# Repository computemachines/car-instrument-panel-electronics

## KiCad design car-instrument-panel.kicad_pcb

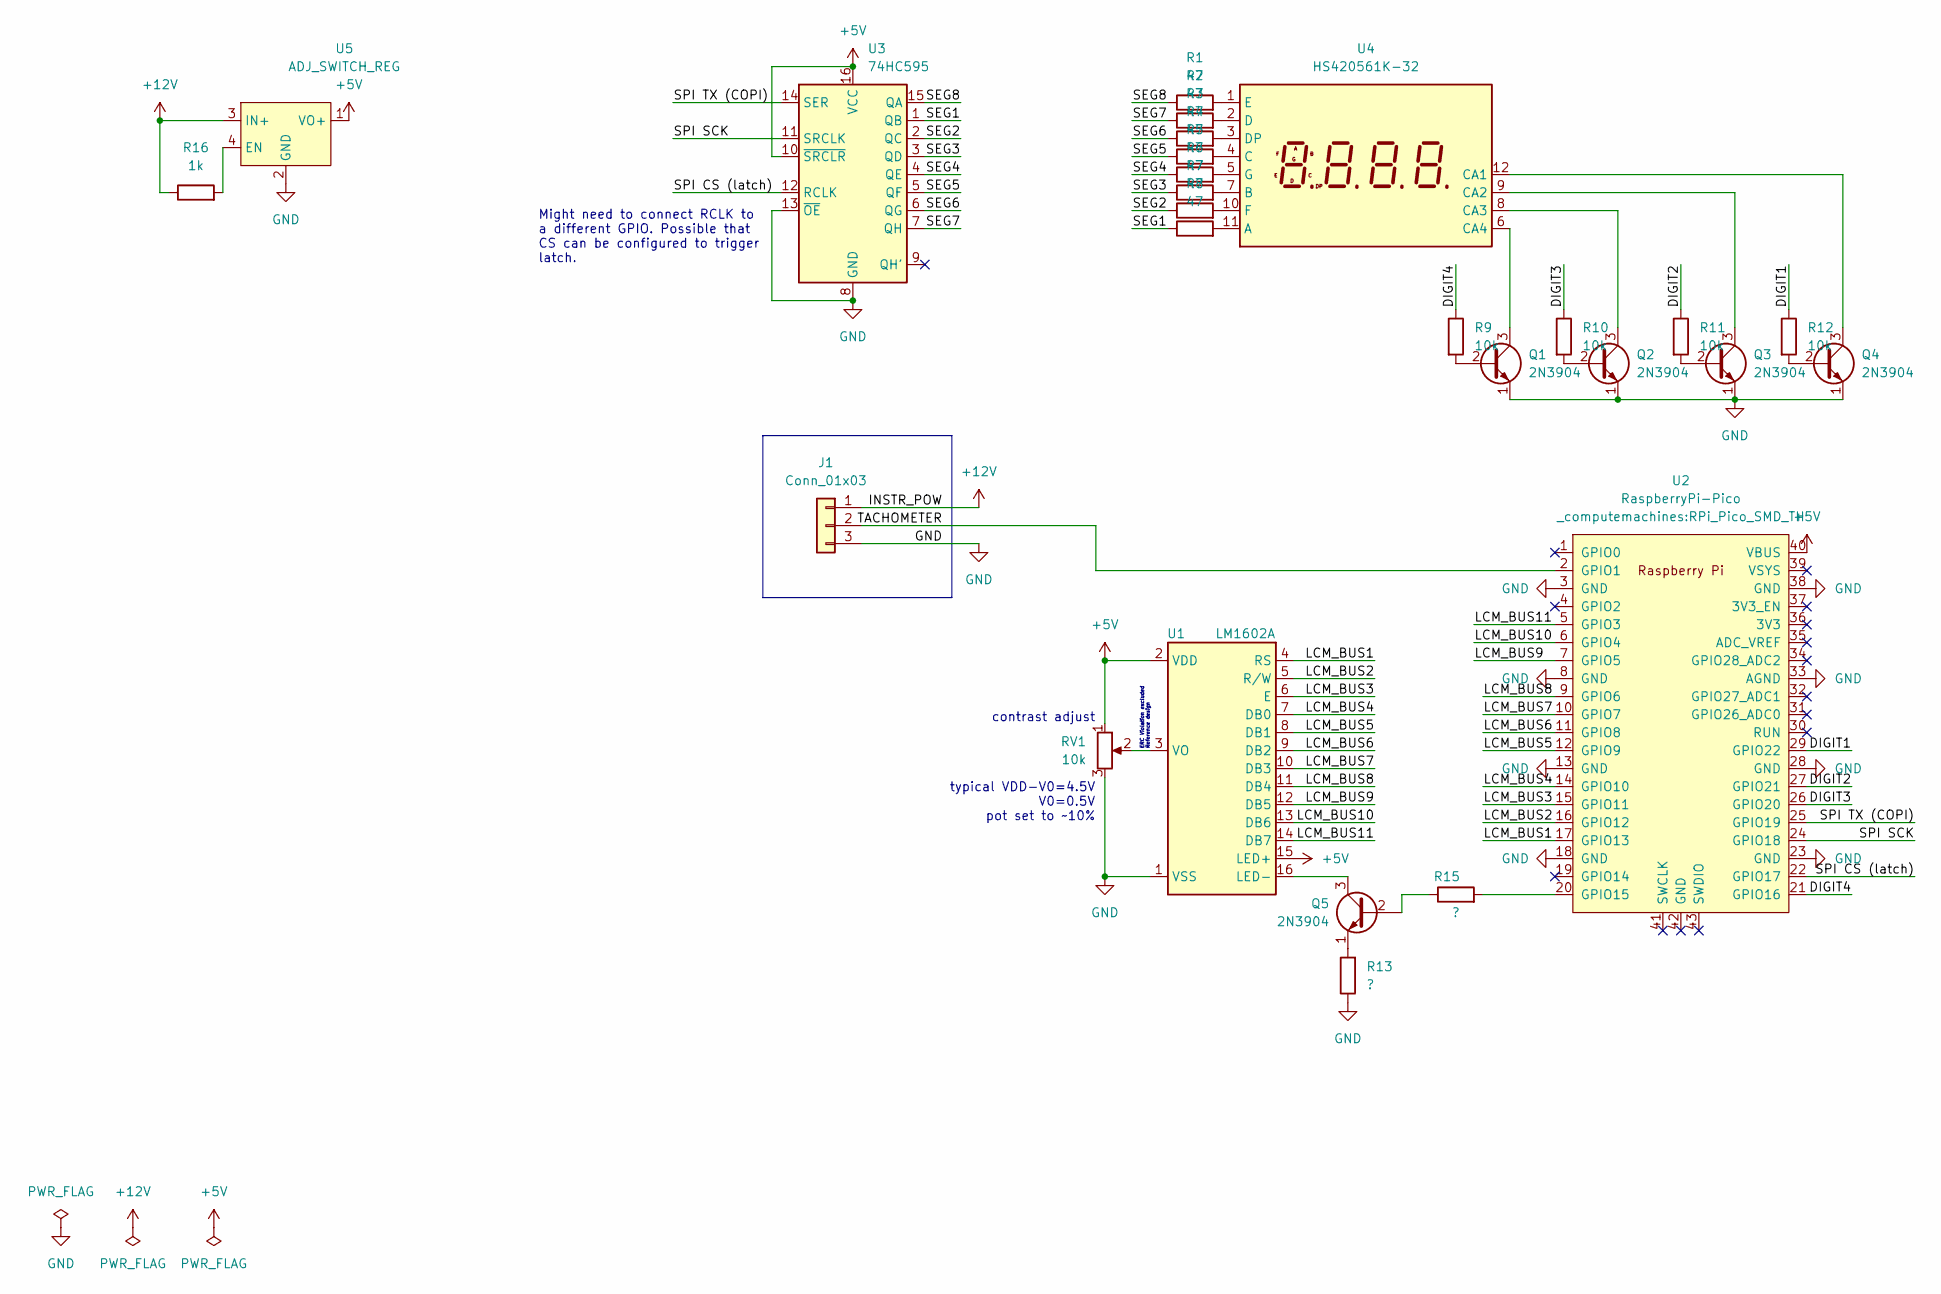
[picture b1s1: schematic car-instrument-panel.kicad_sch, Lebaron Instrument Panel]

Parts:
J1: Conn_01x03; PinHeader_1x03_P2.54mm_Vertical
Q1, Q2, Q3, Q4, Q5: 2N3904; TO-92_Inline
R1, R2, R3, R4, R5, R6, R7, R8: 47; R_Axial_DIN0207_L6.3mm_D2.5mm_P10.16mm_Horizontal
R9, R10, R11, R12: 10k; R_Axial_DIN0207_L6.3mm_D2.5mm_P10.16mm_Horizontal
R13, R15: ?; R_Axial_DIN0207_L6.3mm_D2.5mm_P10.16mm_Horizontal
R16: 1k; R_Axial_DIN0207_L6.3mm_D2.5mm_P10.16mm_Horizontal
RV1: 10k; Potentiometer_ACP_CA9-V10_Vertical
U1: LM1602A; LCM1602A
U2: RaspberryPi-Pico; RPi_Pico_SMD_TH
U3: 74HC595; DIP-16_W7.62mm
U4: HS420561K-32
U5: ADJ_SWITCH_REG; Adjust_Switch_Regulator_Module_B08R6337QY

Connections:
+5V: RV1.1, U1.2 (VDD), U1.15 (LED+), U2.40 (VBUS), U3.10 (~SRCLR), U3.16 (VCC), U5.1 (VO+)
+12V: J1.1, R16.1, U5.3 (IN+)
/DIGIT1: R12.1, U2.29 (GPIO22)
/DIGIT2: R11.1, U2.27 (GPIO21)
/DIGIT3: R10.1, U2.26 (GPIO20)
/DIGIT4: R9.1, U2.21 (GPIO16)
/LCM_BUS1: U1.4 (RS), U2.17 (GPIO13)
/LCM_BUS2: U1.5 (R/W), U2.16 (GPIO12)
/LCM_BUS3: U1.6 (E), U2.15 (GPIO11)
/LCM_BUS4: U1.7 (DB0), U2.14 (GPIO10)
/LCM_BUS5: U1.8 (DB1), U2.12 (GPIO9)
/LCM_BUS6: U1.9 (DB2), U2.11 (GPIO8)
/LCM_BUS7: U1.10 (DB3), U2.10 (GPIO7)
/LCM_BUS8: U1.11 (DB4), U2.9 (GPIO6)
/LCM_BUS9: U1.12 (DB5), U2.7 (GPIO5)
/LCM_BUS10: U1.13 (DB6), U2.6 (GPIO4)
/LCM_BUS11: U1.14 (DB7), U2.5 (GPIO3)
/SEG1: R8.1, U3.1 (QB)
/SEG2: R7.1, U3.2 (QC)
/SEG3: R6.1, U3.3 (QD)
/SEG4: R5.1, U3.4 (QE)
/SEG5: R4.1, U3.5 (QF)
/SEG6: R3.1, U3.6 (QG)
/SEG7: R2.1, U3.7 (QH)
/SEG8: R1.1, U3.15 (QA)
/SPI CS (latch): U2.22 (GPIO17), U3.12 (RCLK)
/SPI SCK: U2.24 (GPIO18), U3.11 (SRCLK)
/SPI TX (COPI): U2.25 (GPIO19), U3.14 (SER)
/TACHOMETER: J1.2, U2.2 (GPIO1)
GND: J1.3, Q1.1 (E), Q2.1 (E), Q3.1 (E), Q4.1 (E), R13.1, RV1.3, U1.1 (VSS), U2.3 (GND), U2.8 (GND), U2.13 (GND), U2.18 (GND), U2.23 (GND), U2.28 (GND), U2.33 (AGND), U2.38 (GND), U3.8 (GND), U3.13 (~OE), U5.2 (GND)
unnamed: Q1.2 (B), R9.2
unnamed: Q1.3 (C), U4.6 (CA4)
unnamed: Q2.2 (B), R10.2
unnamed: Q2.3 (C), U4.8 (CA3)
unnamed: Q3.2 (B), R11.2
unnamed: Q3.3 (C), U4.9 (CA2)
unnamed: Q4.2 (B), R12.2
unnamed: Q4.3 (C), U4.12 (CA1)
unnamed: Q5.1 (E), R13.2
unnamed: Q5.2 (B), R15.1
unnamed: Q5.3 (C), U1.16 (LED-)
unnamed: R1.2, U4.1 (E)
unnamed: R2.2, U4.2 (D)
unnamed: R3.2, U4.3 (DP)
unnamed: R4.2, U4.4 (C)
unnamed: R5.2, U4.5 (G)
unnamed: R6.2, U4.7 (B)
unnamed: R7.2, U4.10 (F)
unnamed: R8.2, U4.11 (A)
unnamed: RV1.2, U1.3 (VO)
unnamed: R15.2, U2.20 (GPIO15)
unnamed: R16.2, U5.4 (EN)

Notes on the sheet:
typical VDD-V0=4.5V V0=0.5V pot set to ~10%
ERC Violation excluded Reference design
contrast adjust
Might need to connect RCLK to a different GPIO. Possible that CS can be configured to trigger latch.

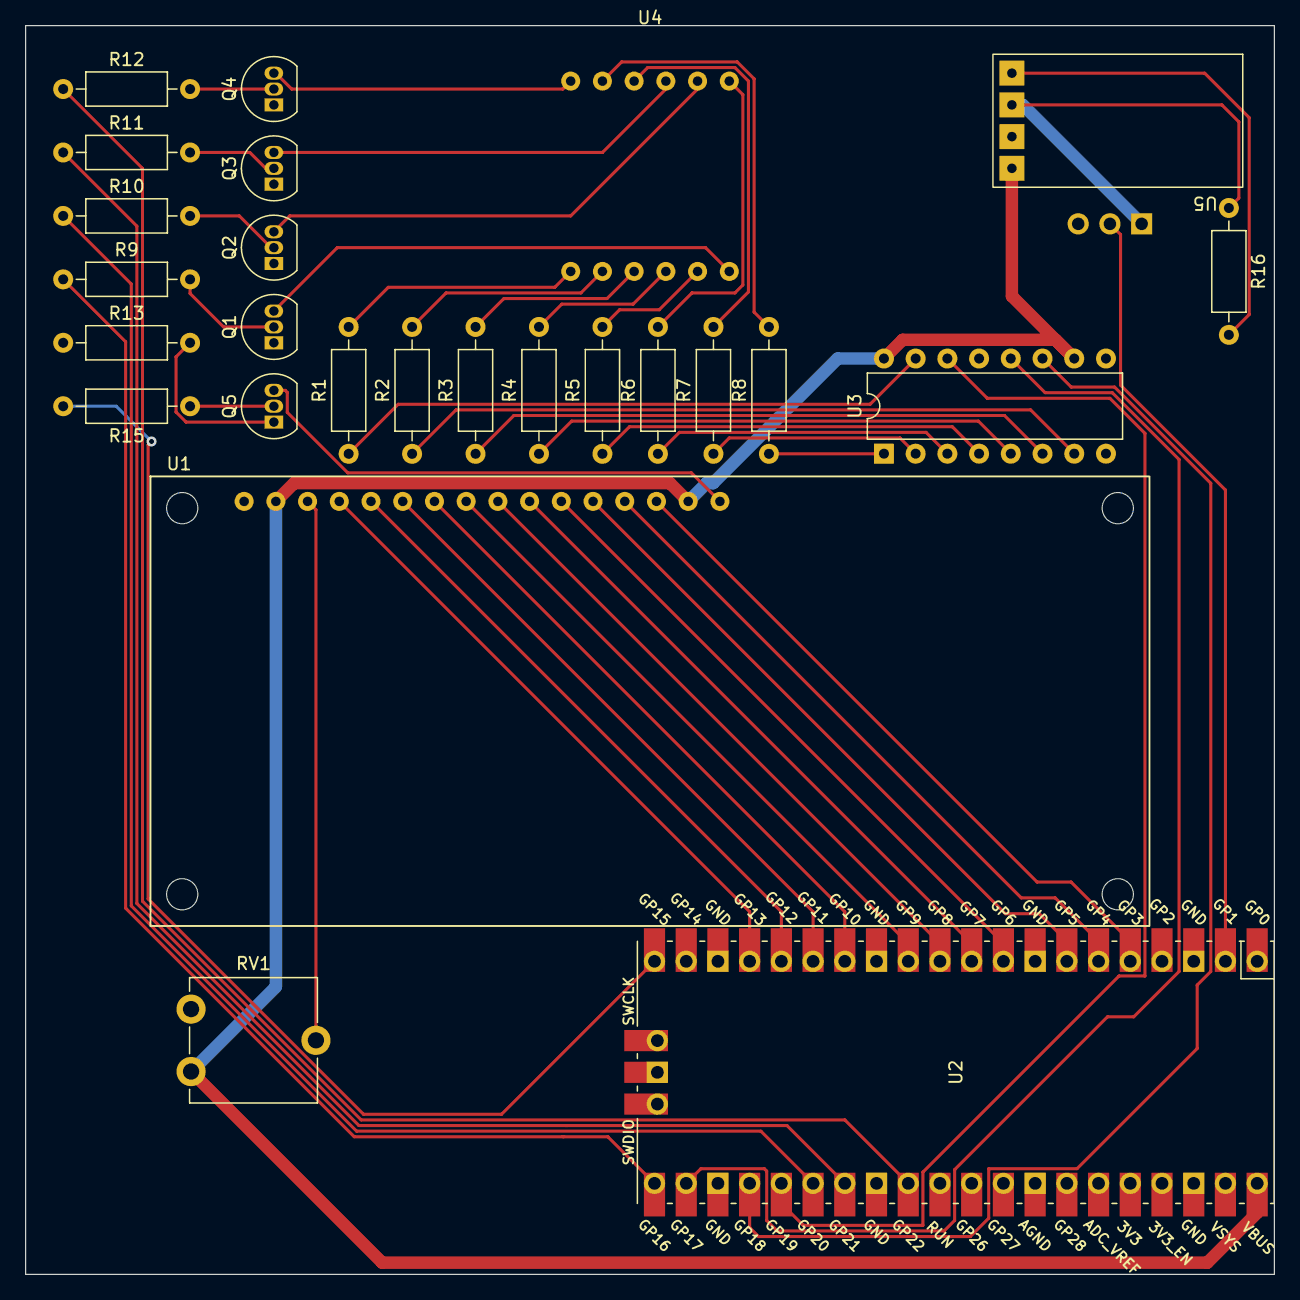
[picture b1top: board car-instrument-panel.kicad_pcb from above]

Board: 2 copper layers, 100.0 x 100.0 mm, 27 parts (1 on the bottom side), 52 nets.

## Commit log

2022-11-19 old changes
